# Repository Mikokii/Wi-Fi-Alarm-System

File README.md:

# Wi-Fi Alarm System

Android App written in Kotlin to control Wi-Fi Alarm System based on HiveMQ.
Wi-Fi module used: ESP8266
Programmed using Arduino IDE

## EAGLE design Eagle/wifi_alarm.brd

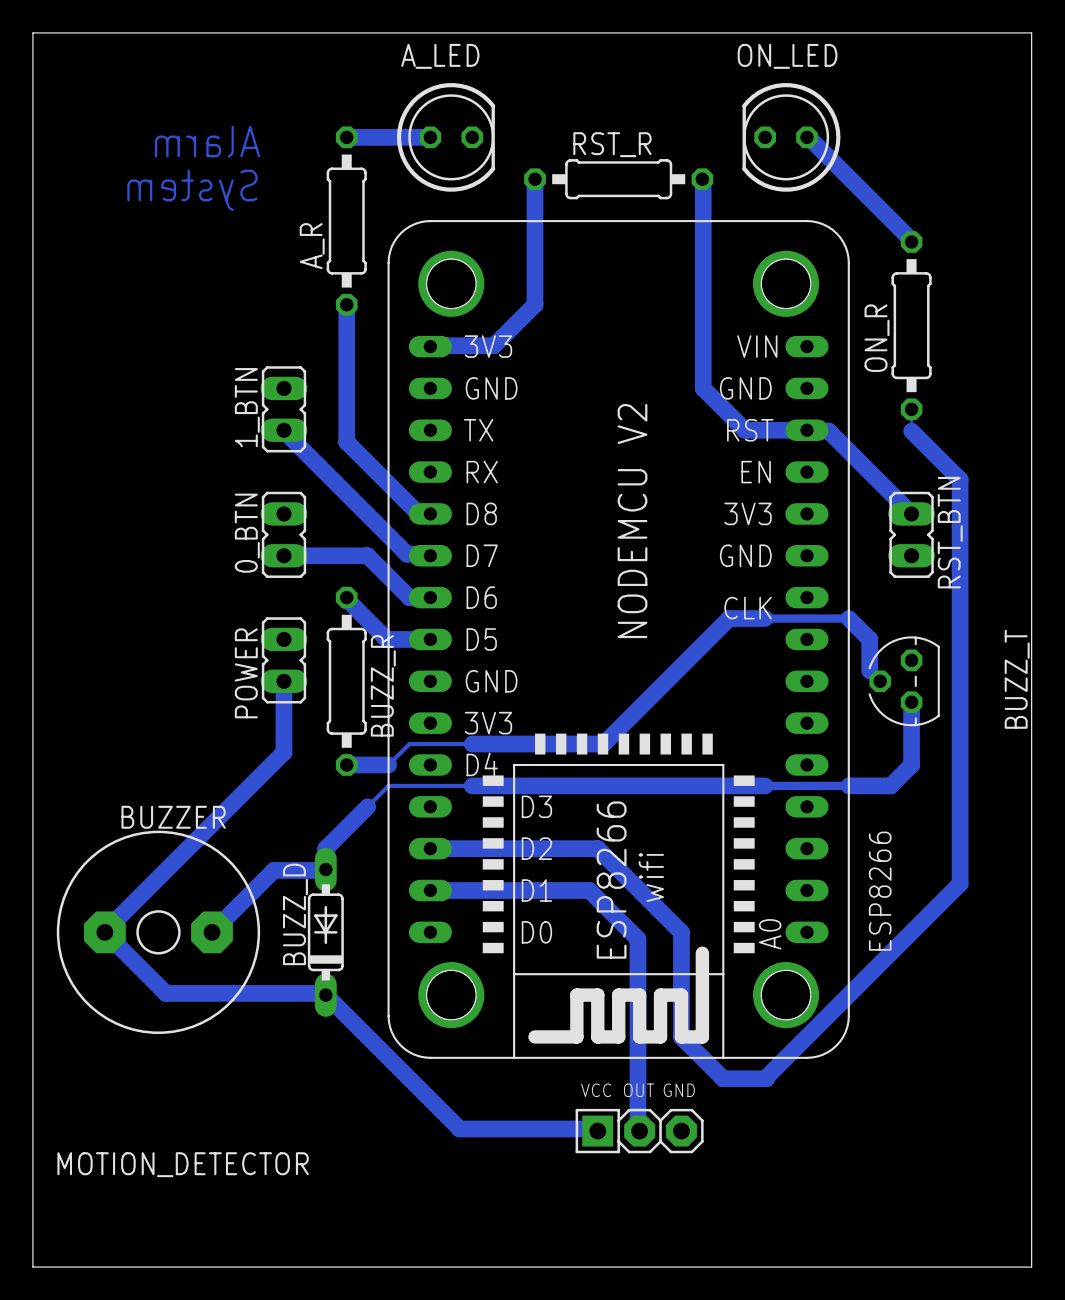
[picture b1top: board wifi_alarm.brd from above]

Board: 2 copper layers, 60.6 x 74.9 mm, 15 parts (0 on the bottom side), 15 nets.

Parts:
0_BTN, 1_BTN: JP1
A_LED: LED5MM
A_R: 22; 0207/10
BUZZER: AL60P
BUZZ_D: 1N4148; DO35-7
BUZZ_R: 1k; 0207/10
BUZZ_T: BC547; TO92
ESP8266: NODEMCU_ESP8266
MOTION_DETECTOR: HC-SR501
ON_LED: LED5MM
ON_R: 100; 0207/10
POWER: JP1
RST_BTN: JP1
RST_R: 10k; 0207/10

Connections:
3V3: ESP8266.3V3@2, ESP8266.3V3@3
+5V: BUZZER.1, BUZZ_D.C, MOTION_DETECTOR.VCC, POWER.1
GND: 0_BTN.2, 1_BTN.2, A_LED.K, BUZZ_T.1, ESP8266.GND@1, ESP8266.GND@2, ESP8266.GND@3, ESP8266.GND@4, MOTION_DETECTOR.GND, ON_LED.K, POWER.2, RST_BTN.2
unnamed: ESP8266.3V3@1, RST_R.1
unnamed: ESP8266.RST, RST_BTN.1, RST_R.2
unnamed: 0_BTN.1, ESP8266.D6
unnamed: 1_BTN.1, ESP8266.D7
unnamed: BUZZER.2, BUZZ_D.A, BUZZ_T.3
unnamed: BUZZ_R.1, ESP8266.D5
unnamed: BUZZ_R.2, BUZZ_T.2
unnamed: A_R.1, ESP8266.D8
unnamed: A_LED.A, A_R.2
unnamed: ESP8266.D2, ON_R.1
unnamed: ON_LED.A, ON_R.2
unnamed: ESP8266.D1, MOTION_DETECTOR.OUT

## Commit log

2024-08-11 Updated .gitignore
2024-08-11 Added test with DHT22
2024-08-11 Added data file to gitignore
2024-08-11 Altered code for movement sensor
2024-08-11 Added WiFi setup template
2024-08-12 Added buzzer and active LED
2024-08-21 Added basic notification system
2024-08-21 Added mqtt connection prototype
2024-08-22 Changed messages and centered
2024-08-22 Added notification permission pop-up and button
2024-08-22 Merged Notifications and alignment changes
2024-08-22 Centered notification settings button
2024-08-22 Deleted notification action and counter
2024-08-23 Added notificiations when movement detected
2024-08-23 Fixed buzzer code for starting
2024-08-23 Added message for starting the alarm system
2024-08-23 Changed topic of the start message
2024-08-24 Added start handling in esp and android
2024-08-24 Added vibration to notification
2024-08-25 Added last will and testament message
2024-08-25 Added receiving messages in ESP
2024-08-25 Added publishing messages in Android
2024-08-26 Added device ON and OFF state handling in android
2024-08-26 Adjusted buzzer actions
2024-08-26 Changed format of the message
2024-08-26 Added publishing sound message in esp
2024-08-26 Added sound control with Android
2024-08-26 Cleaned code in arduino
2024-08-28 Added icons to buttons
2024-08-28 Changed messages to integers
2024-08-28 Finished cleaning code in Arduino file
2024-08-28 Cleaned up Android Studio code
2024-08-29 Changed pin for buzzer
2024-08-29 Added eagle schematics with all parts
2024-09-21 Added buttons
2024-09-21 Added buttons logic
2024-09-21 Changed pinouts for sensor and LED
2024-09-23 Added turning off notification and fixed minor bugs
2024-09-24 Added notifications and vibrations in background
2024-09-25 Eagle Board
2024-09-25 Changed names, values and rearranged Eagle schematics
2025-05-03 Added an icon and a login page
2025-05-05 Added footer, inactive sound button
2025-05-06 Aligned boxes for main activity, changed color
2025-05-13 Working version for mobile apps
2025-05-25 Improved animation
